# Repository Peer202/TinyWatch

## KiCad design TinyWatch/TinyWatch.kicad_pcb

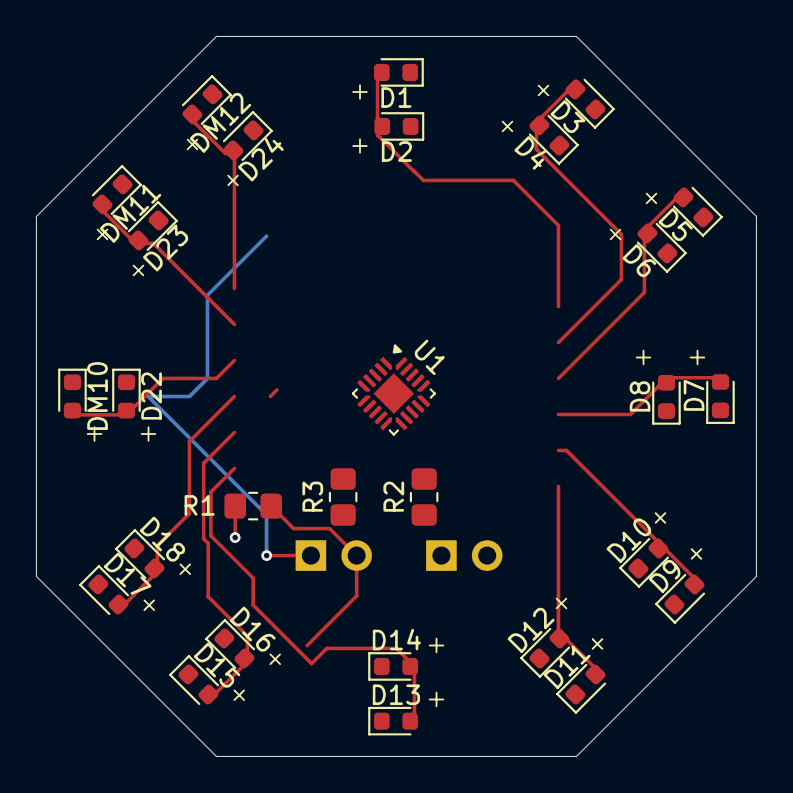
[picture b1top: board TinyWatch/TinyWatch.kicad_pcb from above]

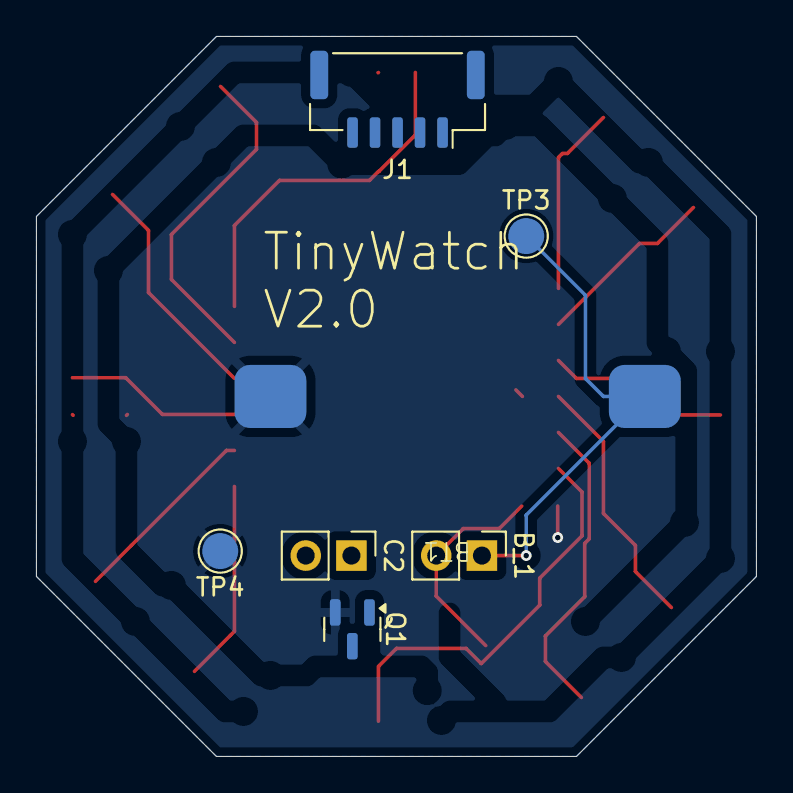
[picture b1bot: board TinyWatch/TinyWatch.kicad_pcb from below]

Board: 4 copper layers, 40.0 x 40.0 mm, 35 parts (7 on the bottom side), 19 nets.

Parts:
BT1: CR2032; Keystone 1070
B_1: Conn_01x02; PinHeader_1x02_P2.54mm_Vertical
C2: Conn_01x02; PinHeader_1x02_P2.54mm_Vertical
D1, D2, D3, D4, D5, D6, D7, D8, D9, D10, D11, D12, D13, D14, D15, D16, D17, D18, D22, D23, D24: LED; LED_0603_1608Metric
DM10, DM11, DM12: LED; LED_0603_1608Metric
J1: DEBUG; JST_GH_SM05B-GHS-TB_1x05-1MP_P1.25mm_Horizontal
Q1: MMBT5551L; SOT-23
R1: 5k; R_0805_2012Metric_Pad1.20x1.40mm_HandSolder
R2, R3: 50; R_0805_2012Metric_Pad1.20x1.40mm_HandSolder
TP3: +3.3V; TestPoint_Pad_D2.0mm
TP4: GND; TestPoint_Pad_D2.0mm
U1: ATtiny416-S; QFN-20-1EP_3x3mm_P0.45mm_EP1.6x1.6mm

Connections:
BT_High: BT1.1 (+), B_1.1, J1.1, TP3.1, U1.1 (VCC)
BT_Low: B_1.2, R1.1, U1.11 (PB0)
GND: BT1.2 (-), J1.4, Q1.2 (E), R1.2, TP4.1, U1.20 (GND)
GND_T_1: Q1.1 (B), U1.19 (PA3)
GS1: D1.1 (K), D3.1 (K), D5.1 (K), D7.1 (K), D9.1 (K), D11.1 (K), D13.1 (K), D15.1 (K), D17.1 (K), DM10.1 (K), DM11.1 (K), DM12.1 (K), R3.1
GS2: D2.1 (K), D4.1 (K), D6.1 (K), D8.1 (K), D10.1 (K), D12.1 (K), D14.1 (K), D16.1 (K), D18.1 (K), D22.1 (K), D23.1 (K), D24.1 (K), R2.1
LED_H_1: D1.2 (A), D2.2 (A), U1.18 (PA2)
LED_H_2: D3.2 (A), D4.2 (A), U1.17 (PA1)
LED_H_3: D5.2 (A), D6.2 (A), U1.15 (PC3)
LED_H_4: D7.2 (A), D8.2 (A), U1.14 (PC2)
LED_H_5: D9.2 (A), D10.2 (A), U1.13 (PC1)
LED_H_6: D11.2 (A), D12.2 (A), U1.12 (PC0)
LED_H_7: D13.2 (A), D14.2 (A), U1.10 (PB1)
LED_H_8: D15.2 (A), D16.2 (A), U1.7 (PB4)
LED_H_9: D17.2 (A), D18.2 (A), U1.6 (PB5)
LED_H_10: D22.2 (A), DM10.2 (A), U1.5 (PA7)
LED_H_11: D23.2 (A), DM11.2 (A), U1.4 (PA6)
LED_H_12: D24.2 (A), DM12.2 (A), U1.3 (PA5)
UPDI: J1.2, U1.16 (~RESET/PA0)

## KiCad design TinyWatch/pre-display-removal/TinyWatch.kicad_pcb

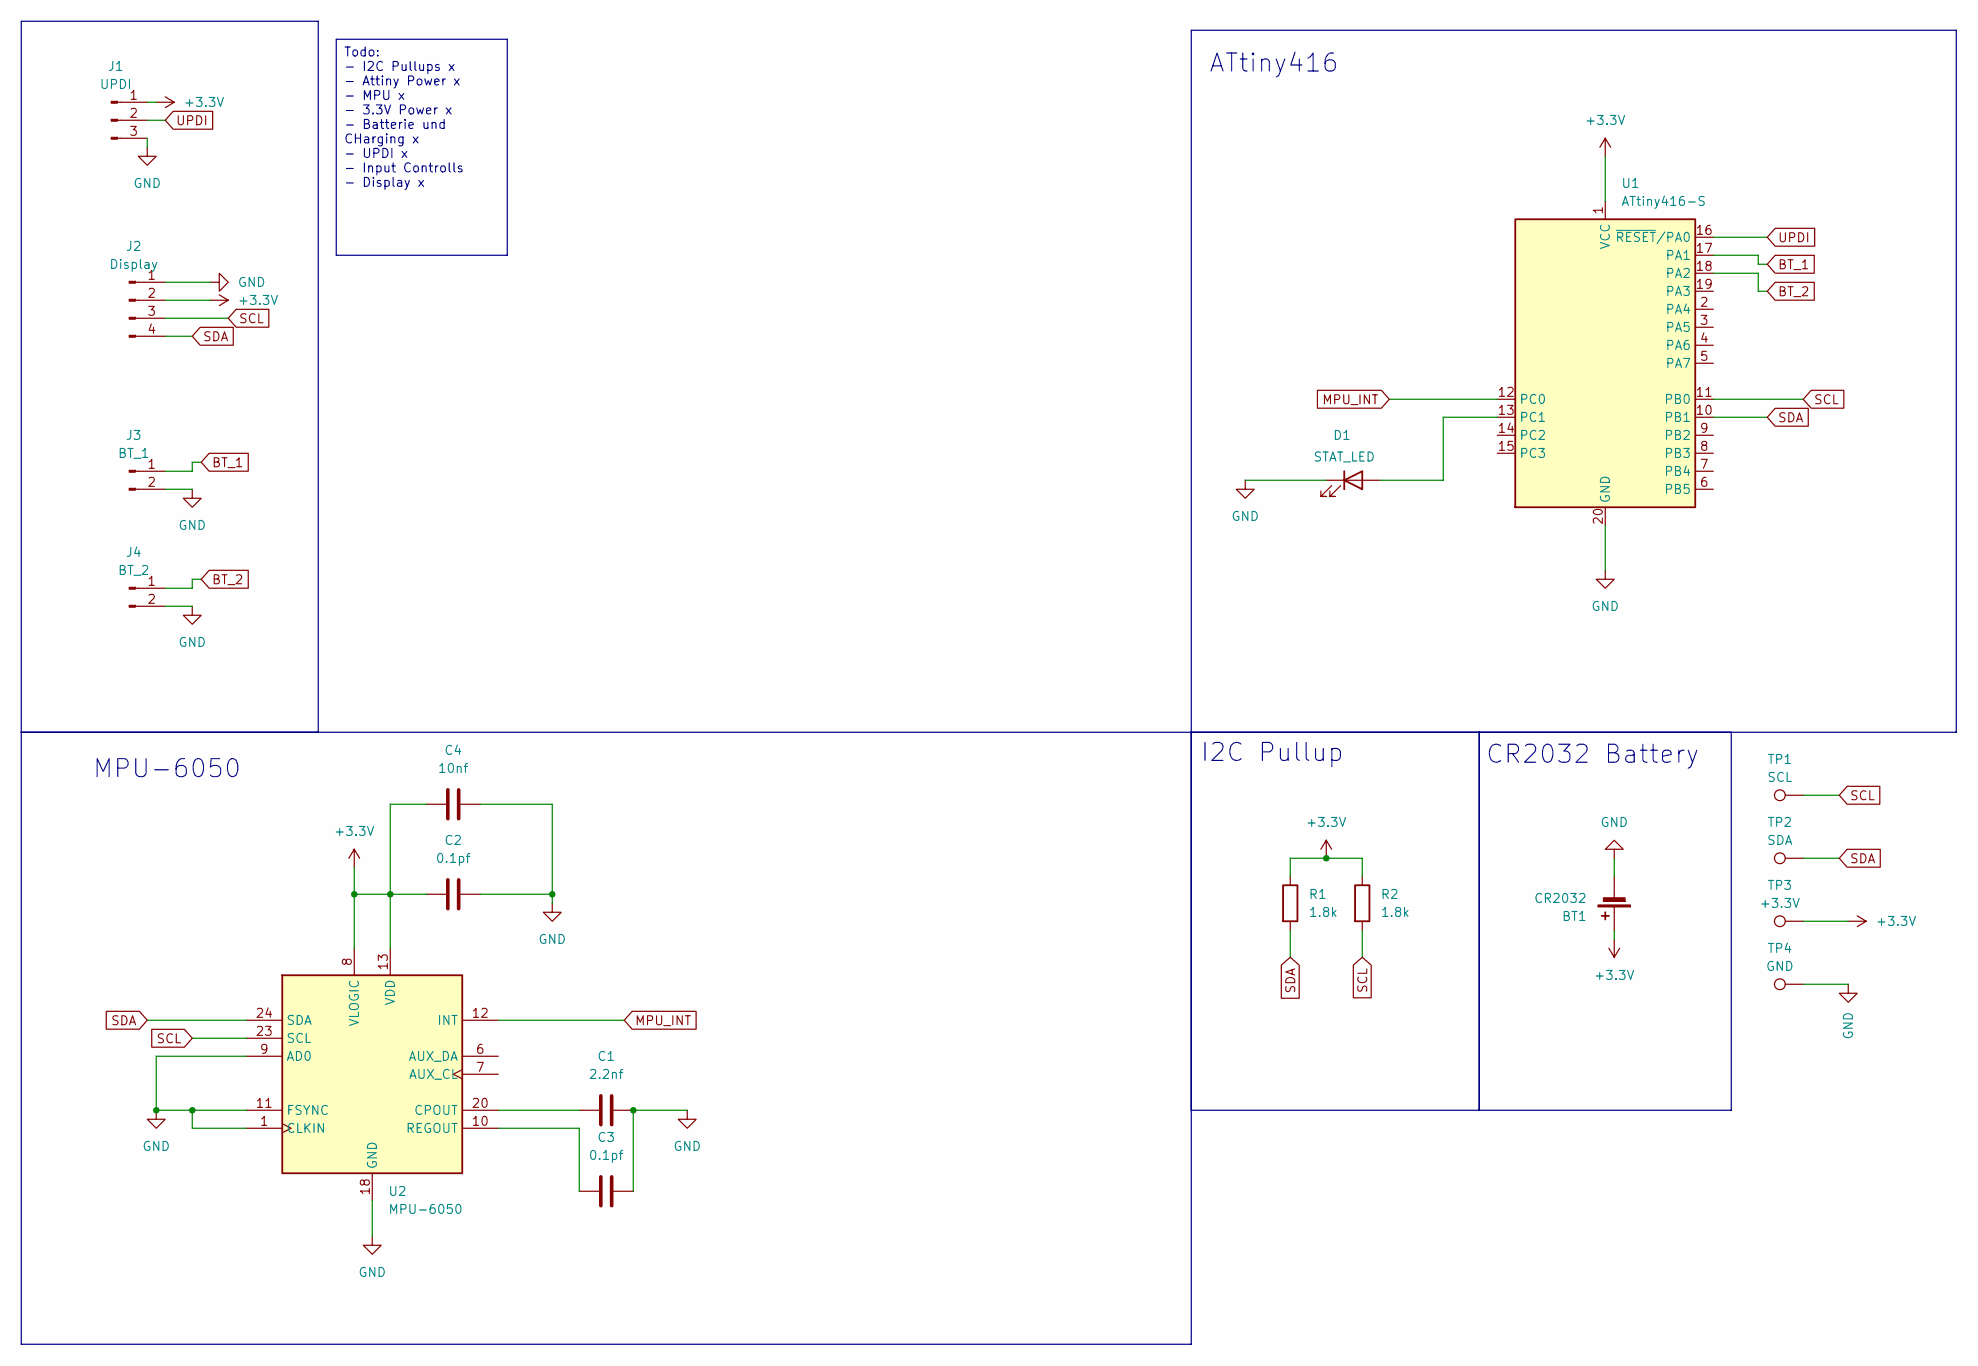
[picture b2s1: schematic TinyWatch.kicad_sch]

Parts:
BT1: CR2032; BatteryHolder_Multicomp_BC-2001_1x2032
C1: 2.2nf; C_0805_2012Metric_Pad1.18x1.45mm_HandSolder
C2, C3: 0.1pf; C_0805_2012Metric_Pad1.18x1.45mm_HandSolder
C4: 10nf; C_0805_2012Metric_Pad1.18x1.45mm_HandSolder
D1: STAT_LED; LED_0805_2012Metric_Pad1.15x1.40mm_HandSolder
J1: UPDI; PinHeader_1x03_P2.54mm_Vertical
J2: Display; PinHeader_1x04_P2.54mm_Vertical
J3: BT_1; PinHeader_1x02_P2.54mm_Vertical
J4: BT_2; PinHeader_1x02_P2.54mm_Vertical
R1, R2: 1.8k; R_0805_2012Metric_Pad1.20x1.40mm_HandSolder
TP1: SCL; TestPoint_Pad_D2.0mm
TP2: SDA; TestPoint_Pad_D2.0mm
TP3: +3.3V; TestPoint_Pad_D2.0mm
TP4: GND; TestPoint_Pad_D2.0mm
U1: ATtiny416-S; SOIC-20W_7.5x12.8mm_P1.27mm
U2: MPU-6050; InvenSense_QFN-24_4x4mm_P0.5mm

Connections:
+3.3V: BT1.1 (+), C2.1, C4.1, J1.1, J2.2, R1.1, R2.1, TP3.1, U1.1 (VCC), U2.8 (VLOGIC), U2.13 (VDD)
BT_1: J3.1, U1.17 (PA1)
BT_2: J4.1, U1.18 (PA2)
GND: BT1.2 (-), C1.2, C2.2, C3.2, C4.2, D1.1 (K), J1.3, J2.1, J3.2, J4.2, TP4.1, U1.20 (GND), U2.1 (CLKIN), U2.9 (AD0), U2.11 (FSYNC), U2.18 (GND)
MPU_INT: U1.12 (PC0), U2.12 (INT)
unnamed: D1.2 (A), U1.13 (PC1)
unnamed: C1.1, U2.20 (CPOUT)
unnamed: C3.1, U2.10 (REGOUT)
SCL: J2.3, R2.2, TP1.1, U1.11 (PB0), U2.23 (SCL)
SDA: J2.4, R1.2, TP2.1, U1.10 (PB1), U2.24 (SDA)
UPDI: J1.2, U1.16 (~RESET/PA0)

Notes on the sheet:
Todo: - I2C Pullups x - Attiny Power x - MPU x - 3.3V Power x - Batterie und CHarging x - UPDI x - Input Controlls - Display x
CR2032 Battery
MPU-6050
ATtiny416
I2C Pullup

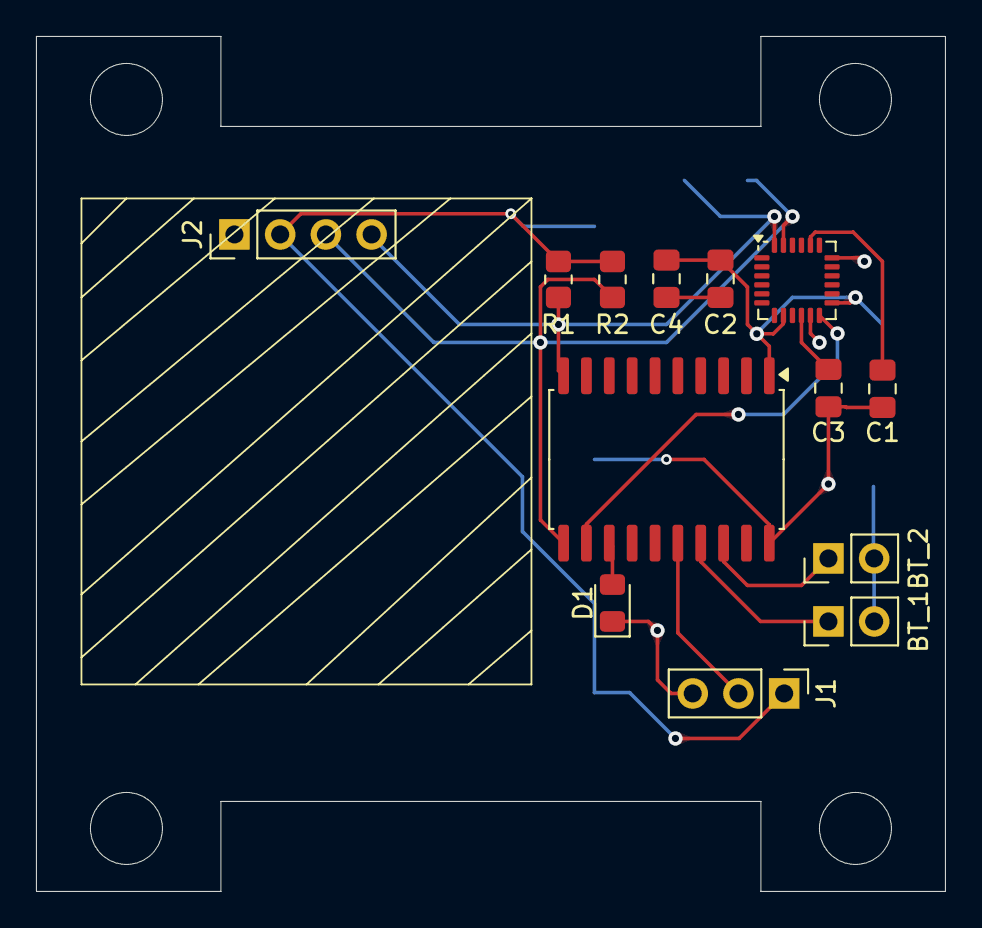
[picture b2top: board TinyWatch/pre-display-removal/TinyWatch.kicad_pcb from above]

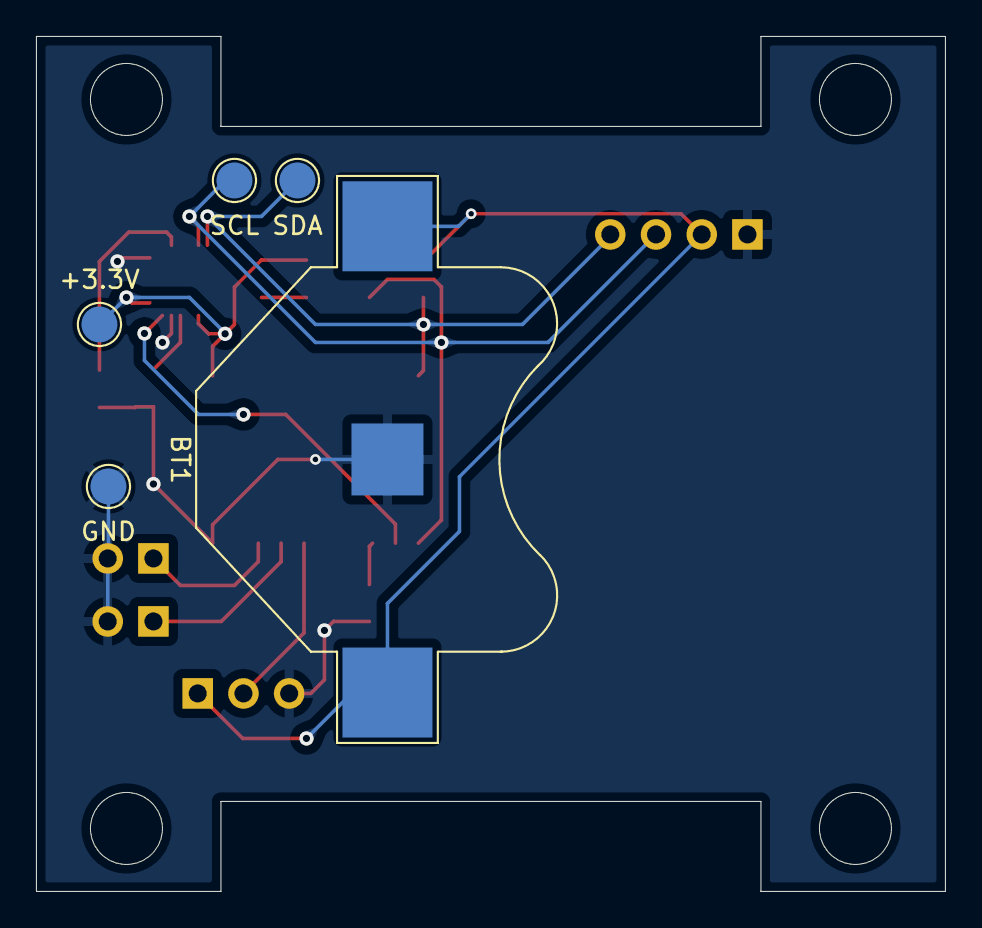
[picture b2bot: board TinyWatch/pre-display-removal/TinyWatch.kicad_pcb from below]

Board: 2 copper layers, 50.5 x 47.5 mm, 18 parts (5 on the bottom side), 11 nets.

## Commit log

2024-11-17 Init Commit Board
2024-11-17 Init Commit Code
2024-11-17 update Git Ignore
2024-11-17 Add Documentation
2024-11-22 Update: First Test Code
2024-11-22 Add Issues assembly Board .1
2024-11-22 Add BOM
2024-11-23 LED Check Code added
2024-11-24 Flicker Tuning
2024-11-24 Fix glowing LED and Switch back from demo code
2024-11-24 Move Display Code to displayhandler.cpp
2024-11-24 Remove display code to external file
2024-11-24 Add Time init prototype
2024-11-24 Add Time Incrementation
2024-11-24 Change Time Init Function Name
2024-12-07 Get PIT working by using non-arduino Blink function
2024-12-07 update upload config
2024-12-08 Rewrite Code to remove Arduino dependency in favor of avr-lib-c
2024-12-08 remove old broken debugblink function
2024-12-10 Renaming Functions to reflect what they actually do
2024-12-10 continue rename
2024-12-10 Rewriting the Time display code to use AVR Libc
2024-12-10 Add Button interrupt
2024-12-10 Cleanup
2024-12-15 Add CAD Files
2024-12-15 Export Step File from Board
2024-12-15 Re-enable time initiation from compile time
2025-04-16 Tried to get UART Working ( Something weird is going on)
2025-04-16 Analyzing current stage of the Project
2025-04-16 Started Reworking the Board
